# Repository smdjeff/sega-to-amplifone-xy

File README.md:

# sega-to-amplifone-vector
Sega G80 vector to Atari Amplifone adapter

* Converts Sega's vector outputs to Atari Amplifone levels and provides buffering.
* Input supply is +5V.
* The board makes +/-12v +/-9v and +0.5v on board.
* High quality TLE2082CP can be used to double bandwidth and slew vs older TL082 op-amps.
* Doubles voltage for X & Y to reduce stress on Sega XY game board amplifiers 
* Corrects black level and scale for RGB color signals
* Simulated Sega G08 vector impedance for Sega XY board

|     | Sega  | Atari |
| --- | ----- | ----- |
| X   | +/-4v | +/-8v |
| Y   | +/-3v | +/-6v |
| R   | 0-4v  | 1.0-3.5v |
| G   | 0-4v  | 1.0-3.5v |
| B   | 0-4v  | 1.0-3.5v |

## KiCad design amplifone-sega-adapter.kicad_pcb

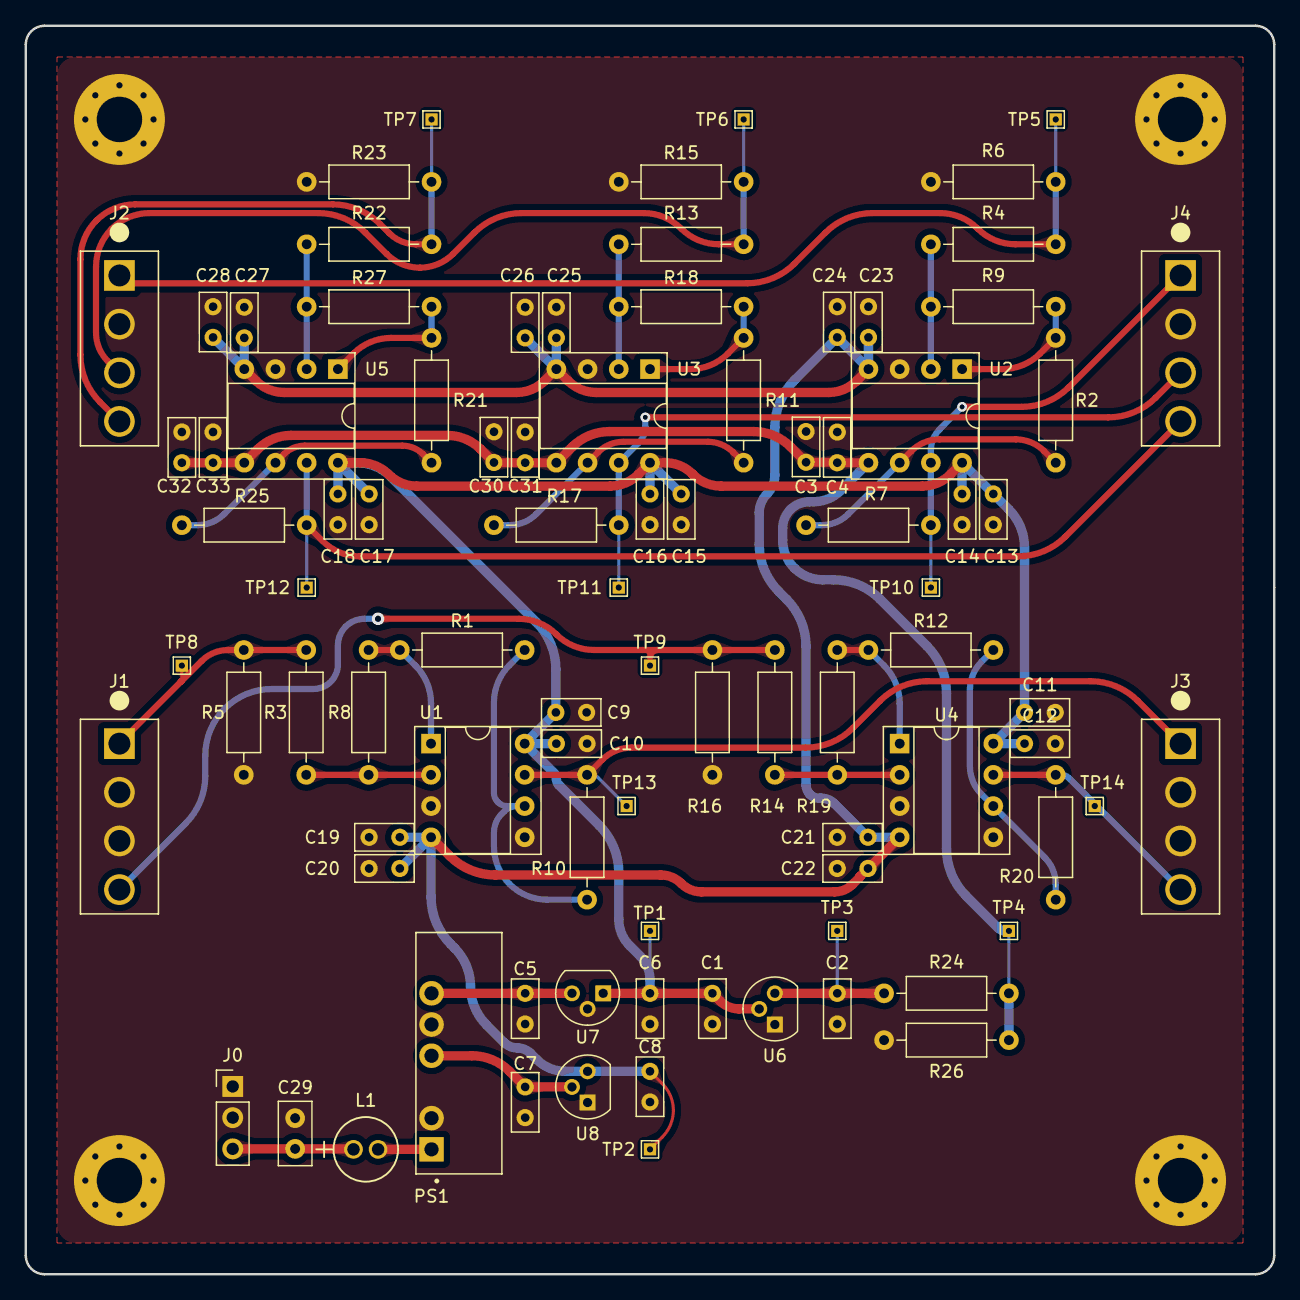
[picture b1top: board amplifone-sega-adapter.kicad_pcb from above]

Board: 2 copper layers, 101.6 x 101.6 mm, 93 parts (0 on the bottom side), 34 nets.

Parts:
C1, C2: 1uF; C_Rect_L4.6mm_W2.0mm_P2.50mm_MKS02_FKP02
C3, C10, C12, C14, C16, C18, C20, C22, C24, C26, C28, C30, C32: .01uF; C_Rect_L4.6mm_W2.0mm_P2.50mm_MKS02_FKP02
C4, C6, C8, C9, C11, C13, C15, C17, C19, C21, C23, C25, C27, C31, C33: .1uF; C_Rect_L4.6mm_W2.0mm_P2.50mm_MKS02_FKP02
C5, C7: .33uF; C_Rect_L4.6mm_W2.0mm_P2.50mm_MKS02_FKP02
C29: 10uF CER; C_Disc_D5.0mm_W2.5mm_P2.50mm
H1, H2, H3, H4: MountingHole_Pad; MountingHole_3.7mm_Pad_Via
J0: Conn_01x03_Male; PinHeader_1x03_P2.54mm_Vertical
J1, J2, J3, J4: 640385-4; TE_640385-4
L1: 22uH; 1100R_MUR
PS1: RD-0512D; CONV_RD-0512D
R1, R2, R3, R4, R7, R11, R12, R13, R14, R17, R21, R22, R25: 10k; R_Axial_DIN0207_L6.3mm_D2.5mm_P10.16mm_Horizontal
R5, R16: 14k; R_Axial_DIN0207_L6.3mm_D2.5mm_P10.16mm_Horizontal
R6, R15, R23: 2.7k; R_Axial_DIN0207_L6.3mm_D2.5mm_P10.16mm_Horizontal
R8, R19: 10K; R_Axial_DIN0207_L6.3mm_D2.5mm_P10.16mm_Horizontal
R9, R18, R27: 6.3k; R_Axial_DIN0207_L6.3mm_D2.5mm_P10.16mm_Horizontal
R10, R20: 20K; R_Axial_DIN0207_L6.3mm_D2.5mm_P10.16mm_Horizontal
R24: 100k; R_Axial_DIN0207_L6.3mm_D2.5mm_P10.16mm_Horizontal
R26: 50k; R_Axial_DIN0207_L6.3mm_D2.5mm_P10.16mm_Horizontal
TP1, TP2, TP3, TP4, TP5, TP6, TP7, TP8, TP9, TP10, TP11, TP12, TP13, TP14: TestPoint; TestPoint_THTPad_1.0x1.0mm_Drill0.5mm
U1, U2, U3, U4, U5: TL082; DIP-8_W7.62mm_Socket
U6: MCP1702-1502E/TO; TO-92
U7: DI78L09ZAB; TO-92
U8: DI79L09ZAB; TO-92

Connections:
+0V5: C3.1, C4.1, C30.1, C31.1, C32.1, C33.1, R24.1, R26.2, TP4.1, U2.5 (+), U3.5 (+), U5.5 (+)
+1V5: C2.1, R24.2, TP3.1, U6.3 (VO)
+5V: C29.1, J0.3, L1.1
+9V: C1.1, C6.1, C9.1, C10.1, C11.1, C12.1, C13.1, C14.1, C15.1, C16.1, C17.1, C18.1, TP1.1, U1.8 (V+), U2.8 (V+), U3.8 (V+), U4.8 (V+), U5.8 (V+), U6.2 (VI), U7.1 (VO)
+12V: C5.1, PS1.6 (+VOUT), U7.3 (VI)
-9V: C8.1, C19.2, C20.2, C21.2, C22.2, C23.2, C24.2, C25.2, C26.2, C27.2, C28.2, TP2.1, U1.4 (V-), U2.4 (V-), U3.4 (V-), U4.4 (V-), U5.4 (V-), U8.3 (VO)
-12V: C7.1, PS1.4 (-VOUT), U8.2 (VI)
/amplifiers/B_IN: J2.4, R22.1, R23.2, TP7.1
/amplifiers/B_OUT: J4.4, R25.2, TP12.1, U5.7
/amplifiers/G_IN: J2.3, R13.1, R15.2, TP6.1
/amplifiers/G_OUT: J4.3, R17.2, TP11.1, U3.7
/amplifiers/R_IN: J2.1, R4.1, R6.2, TP5.1
/amplifiers/R_OUT: J4.1, R7.2, TP10.1, U2.7
/amplifiers/X_IN: J1.1, R3.1, R5.1, TP8.1
/amplifiers/X_OUT: J3.1, R10.2, TP13.1, U1.7
/amplifiers/Y_IN: J1.4, R14.1, R16.1, TP9.1
/amplifiers/Y_OUT: J3.4, R20.2, TP14.1, U4.7
GND: C1.2, C2.2, C3.2, C4.2, C5.2, C6.2, C7.2, C8.2, C9.2, C10.2, C11.2, C12.2, C13.2, C14.2, C15.2, C16.2, C17.2, C18.2, C19.1, C20.1, C21.1, C22.1, C23.1, C24.1, C25.1, C26.1, C27.1, C28.1, C29.2, C30.2, C31.2, C32.2, C33.2, H1.1, H2.1, H3.1, H4.1, J0.1, J0.2, J1.2, J1.3, J2.2, J3.2, J3.3, J4.2, PS1.2 (-VIN), PS1.5 (COM), R5.2, R6.1, R15.1, R16.2, R23.1, R26.1, U1.3 (+), U1.5 (+), U2.3 (+), U3.3 (+), U4.3 (+), U4.5 (+), U5.3 (+), U6.1 (GND), U7.2 (GND), U8.1 (GND)
unnamed: L1.2, PS1.1 (+VIN)
unnamed: R1.1, R8.2, U1.1
unnamed: R2.1, R9.2, U2.1
unnamed: R11.1, R18.2, U3.1
unnamed: R12.1, R19.2, U4.1
unnamed: R21.1, R27.2, U5.1
unnamed: R3.2, R8.1, U1.2 (-)
unnamed: R1.2, R10.1, U1.6 (-)
unnamed: R4.2, R9.1, U2.2 (-)
unnamed: R2.2, R7.1, U2.6 (-)
unnamed: R13.2, R18.1, U3.2 (-)
unnamed: R11.2, R17.1, U3.6 (-)
unnamed: R14.2, R19.1, U4.2 (-)
unnamed: R12.2, R20.1, U4.6 (-)
unnamed: R22.2, R27.1, U5.2 (-)
unnamed: R21.2, R25.1, U5.6 (-)

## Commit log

2024-06-18 revision 2

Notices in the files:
amplifone-sega-adapter.kicad_pcb:
TRANSLATOR (C)2024
